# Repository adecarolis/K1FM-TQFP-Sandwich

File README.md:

# TQFP Sandwich

## A fully open sourced drop-in replacement for the [DL2MAN Sandwich](https://dl2man.de/)

This sligthly modified version of [Manuel DL2MAN](https://dl2man.de/)'s exceptional project was originally motivated by the need of a proper power connector and a TCXO. Subsequently an SWR meter and a 1.3" oled display were added.

### Boards

#### Main

- ATM328P on TQFP-32 footprint + all SMD components + single side, 2 layers design ($2 per 5 bare PCBs at JLCPCB)
- Available CPL and BOM files for rapid prototyping orders (~$39 for 5 fully assembled PCBs at JLCPCB ***)
- Round barrel jack connector compatible with the FT-817 (1.70mm ID - 4.00mm OD)
- Temperature Controlled Oscillator (TCXO) for absolute frequency precision (alignment no longer necessary)
- Extra 0 ohm resistors / contact pads for easier experimenting and troubleshooting

#### UI

- Accepts both 0.96" and 1.3" OLED displays
- Anti-bounce capacitors allowing for low-cost encoders being used
- Optional GPS receiver + antenna (not yet tested)
- Optional LM386 audio amplifier (not yet tested)

#### RF

- Compatible with DL2MAN REV3 standard RF boards
- Onboard SWR/Wattmeter
- High bands design: 10m, 15m, 20m, 30m, 40m
- SMD design allows for using either a single IRLML2060 or three MMBF170's (caps and toroids need to be matched accordingly)
- SMD Relays (Omron G6KU-2G-Y)

*** Parts not available (or currently not in stock) at LCSC that need to be sourced and installed separately: PJ-18H, Si5351, LM4562MAX, ASTX-H11-27.000MHZ-T, FST3253MTCX

### Testing

 This project is to be considered as experimental. If you are looking for stability and reliabiality, I'd recommend sticking to the original. 

| Board | Number built | Remarks                                                      | Issues                                                       |
| :---: | :----------: | ------------------------------------------------------------ | ------------------------------------------------------------ |
| Main  |      4       | - No performance differences from the original found yet.<br />- Only tested with OLED displays. |                                                              |
|  UI   |      5       | - Most 1.3" displays work normally but some require [a software patch](https://groups.io/g/ucx/message/5147?p=,,,20,0,0,0::Created,,reverted,20,2,0,79343439) (this would be the case for all UI boards, not just this particular one). | GPS and audio amplifier (both optional) not yet tested.      |
|  RF   |      1       | - Uses the REV3 IO Extender configuration with 3x SOT23 mosfets therefore passive components can be dimensioned after BS170/MMBF170's or IRLML2060's.<br />- [The SWR meter software](https://github.com/adecarolis/QCX-SSB/tree/swr-meter) modification currently only works for CW when using the straight key. | So far only tested on 20 meters and 40 meters using 3x BS170 mosfets: good performance on 20 meters, not good on 40. |

### License

Creative Commons 3.0

https://creativecommons.org/licenses/by-sa/3.0/

### Disclaimer

COVERED SOFTWARE IS PROVIDED UNDER THIS LICENSE ON AN "AS IS" BASIS, WITHOUT WARRANTY OF ANY KIND, EITHER EXPRESSED OR IMPLIED, INCLUDING, WITHOUT LIMITATION, WARRANTIES THAT THE COVERED SOFTWARE IS FREE OF DEFECTS, MERCHANTABLE, FIT FOR A PARTICULAR PURPOSE OR NON-INFRINGING. THE ENTIRE RISK AS TO THE QUALITY AND PERFORMANCE OF THE COVERED SOFTWARE IS WITH YOU. SHOULD ANY COVERED SOFTWARE PROVE DEFECTIVE IN ANY RESPECT, YOU (NOT THE INITIAL DEVELOPER OR ANY OTHER CONTRIBUTOR) ASSUME THE COST OF ANY NECESSARY SERVICING, REPAIR OR CORRECTION. THIS DISCLAIMER OF WARRANTY CONSTITUTES AN ESSENTIAL PART OF THIS LICENSE. NO USE OF ANY COVERED SOFTWARE IS AUTHORIZED HEREUNDER EXCEPT UNDER THIS DISCLAIMER.

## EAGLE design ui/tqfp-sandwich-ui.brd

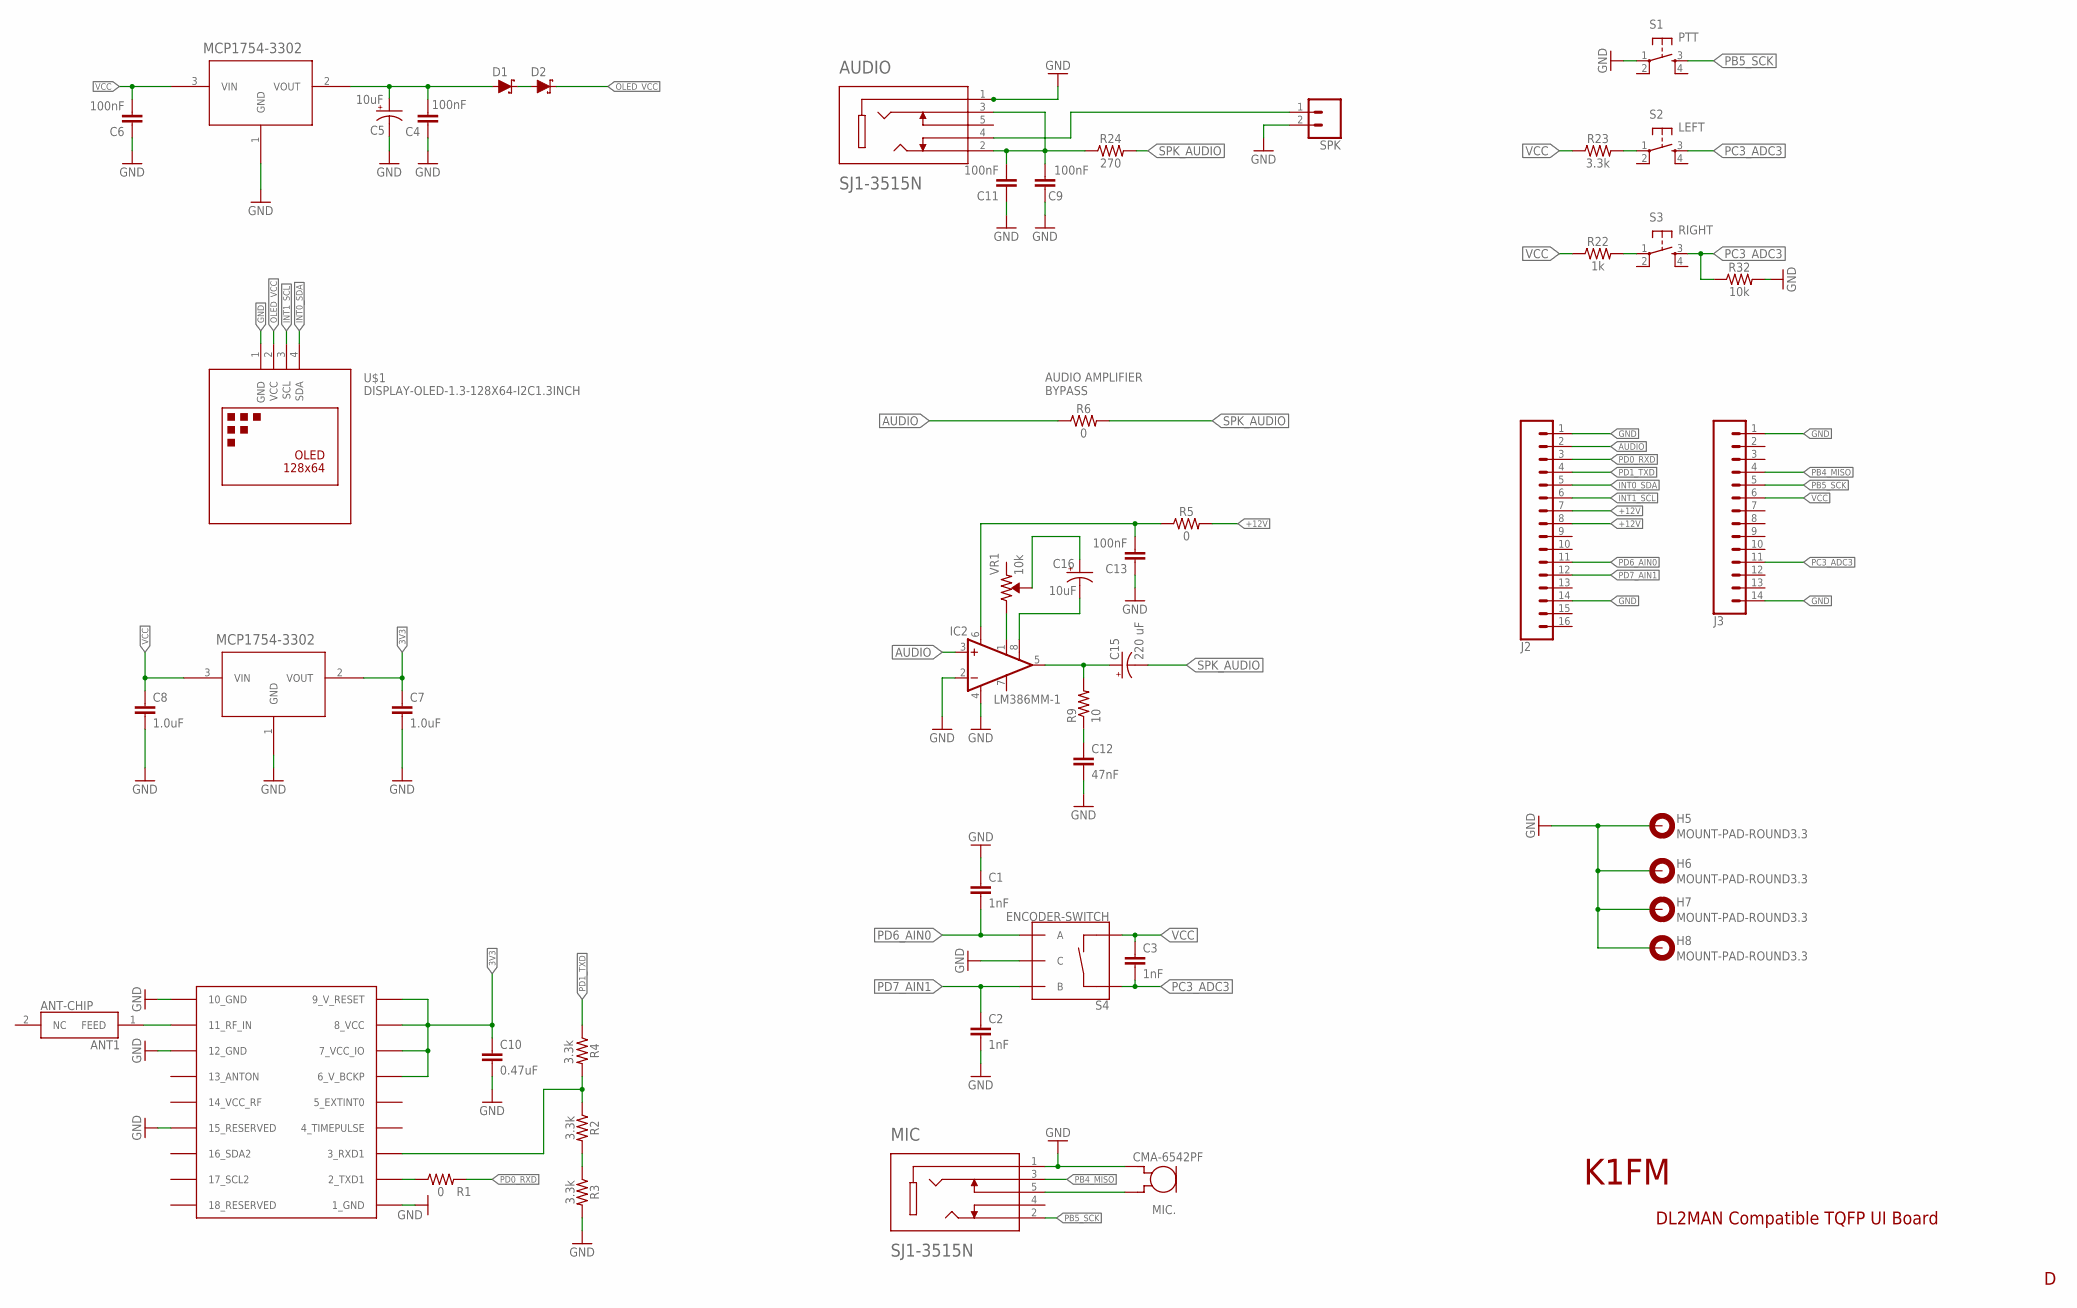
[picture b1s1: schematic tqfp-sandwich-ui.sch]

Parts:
ANT-CHIP: ANT1; 1575AT43A0040E
AUDIO: SJ1-3515N; CUI_SJ1-3515N
C1, C2, C3: 1nF; 0603
C4, C6, C9, C11, C13: 100nF; 0603
C5, C16: 10uF; EIA3216
C7, C8: 1.0uF; 0603
C10: 0.47uF; 0603
C12: 47nF; 0603
C15: 220 uF; PANASONIC_C
D1, D2: 1A/23V/620mV; SOD-323
GPS1: UBLOX_MAX
H5, H6, H7, H8: MOUNT-PAD-ROUND3.3; 3,3-PAD
IC2: LM386MM-1; MMSOP08
J2: CONN_16; 1X16
J3: CONN_14; 1X14
MIC: SJ1-3515N; CUI_SJ1-3515N
MIC.: CMA-6542PF; CUI_CMA-6542PF
R1, R5, R6: 0; 0603
R2, R3, R4, R23: 3.3k; 0603
R9: 10; 0603
R22: 1k; 0603
R24: 270; 0603
R32: 10k; 0603
S1: PTT; DTSM-6
S2: LEFT; DTSM-6
S3: RIGHT; DTSM-6
S4: ENCODER-SWITCH; ROTARY_ENC_PLAIN
SPK: CONN_02; 1X02
U1, U3: MCP1754X-XXXXX/C; SOT-23A_MC
U$1: DISPLAY-OLED-1.3-128X64-I2C1.3INCH; DISPLAY-OLED-1.3-128X64-I2C
VR1: 10k; TRIMPOT-SMD-TC33X

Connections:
3V3: C7.1, C10.1, GPS1.6_V_BCKP, GPS1.7_VCC_IO, GPS1.8_VCC, GPS1.9_V_RESET, U3.2 (VOUT)
+12V: J2.7, J2.8, R5.2
AUDIO: IC2.3 (+IN), J2.2, R6.1
GND: AUDIO.1, C1.1, C2.2, C4.1, C5.-, C6.1, C7.2, C8.2, C9.1, C10.2, C11.1, C12.2, C13.1, GPS1.1_GND, GPS1.10_GND, GPS1.12_GND, GPS1.15_RESERVED, H5.B3,3, H6.B3,3, H7.B3,3, H8.B3,3, IC2.2 (-IN), IC2.4 (GND), J2.1, J2.14, J3.1, J3.14, MIC.1, MIC..GND, R3.2, R32.2, S1.1, S4.C, SPK.2, U1.1 (GND), U3.1 (GND), U$1.1 (GND)
INT0_SDA: J2.5, U$1.4 (SDA)
INT1_SCL: J2.6, U$1.3 (SCL)
unnamed: GPS1.2_TXD1, R1.1
unnamed: MIC.5, MIC..OUT
unnamed: GPS1.3_RXD1, R2.1, R4.2
unnamed: R23.2, S2.1
unnamed: R2.2, R3.1
unnamed: ANT-CHIP.1 (FEED), GPS1.11_RF_IN
unnamed: D1.C, D2.A
unnamed: C4.2, C5.+, D1.A, U1.2 (VOUT)
unnamed: C12.1, R9.1
unnamed: AUDIO.4, SPK.1
unnamed: C15.+, IC2.5 (OUT), R9.2
unnamed: IC2.1 (GAIN), VR1.1 (CW)
unnamed: C16.+, VR1.2 (WIPER)
unnamed: C16.-, IC2.8 (GAIN)
unnamed: C13.2, IC2.6 (VS), R5.1
unnamed: R22.2, S3.1
unnamed: AUDIO.2, AUDIO.3, C9.2, C11.2, R24.1
OLED_VCC: D2.C, U$1.2 (VCC)
PB4_MISO: J3.4, MIC.3
PB5_SCK: J3.5, MIC.2, S1.3
PC3_ADC3: C3.2, J3.11, R32.1, S2.3, S3.3, S4.SW+
PD0_RXD: J2.3, R1.2
PD1_TXD: J2.4, R4.1
PD6_AIN0: C1.2, J2.11, S4.A
PD7_AIN1: C2.1, J2.12, S4.B
SPK_AUDIO: C15.-, R6.2, R24.2
VCC: C3.1, C6.2, C8.1, J3.6, R22.1, R23.1, S4.SW-, U1.3 (VIN), U3.3 (VIN)

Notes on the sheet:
DL2MAN Compatible TQFP UI Board
K1FM
AUDIO AMPLIFIER BYPASS

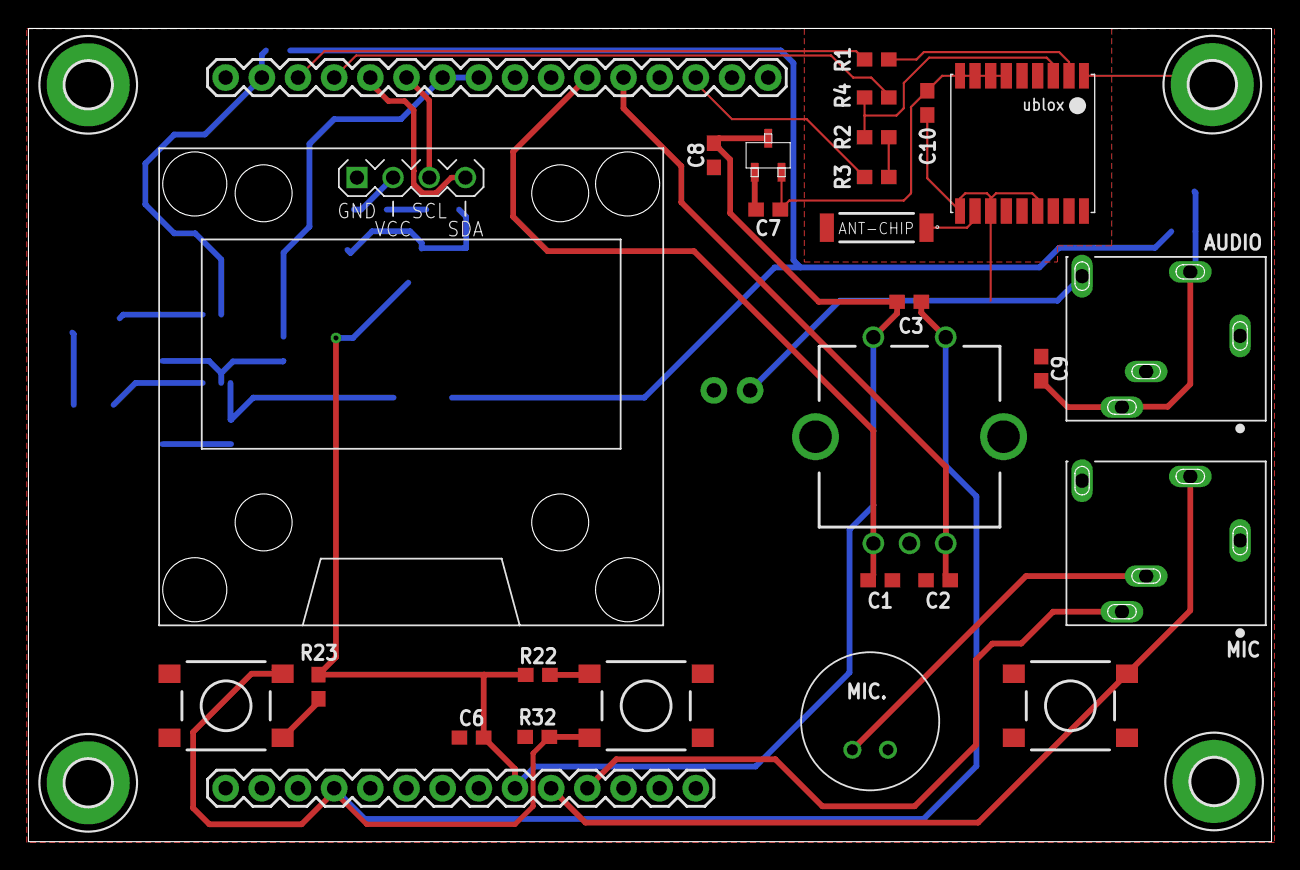
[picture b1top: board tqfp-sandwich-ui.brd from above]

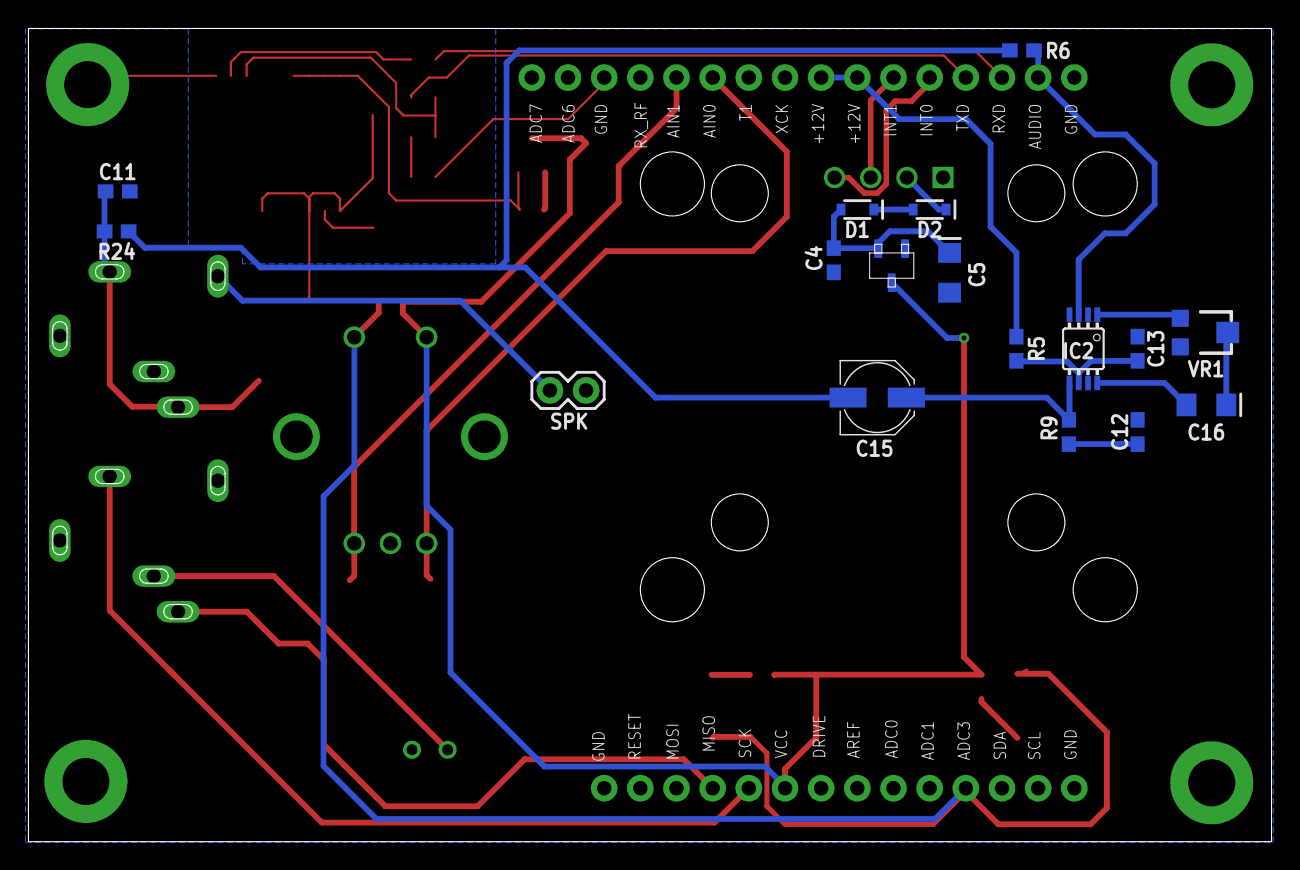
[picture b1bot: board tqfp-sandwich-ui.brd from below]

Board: 2 copper layers, 87.3 x 57.1 mm, 49 parts (17 on the bottom side), 33 nets.

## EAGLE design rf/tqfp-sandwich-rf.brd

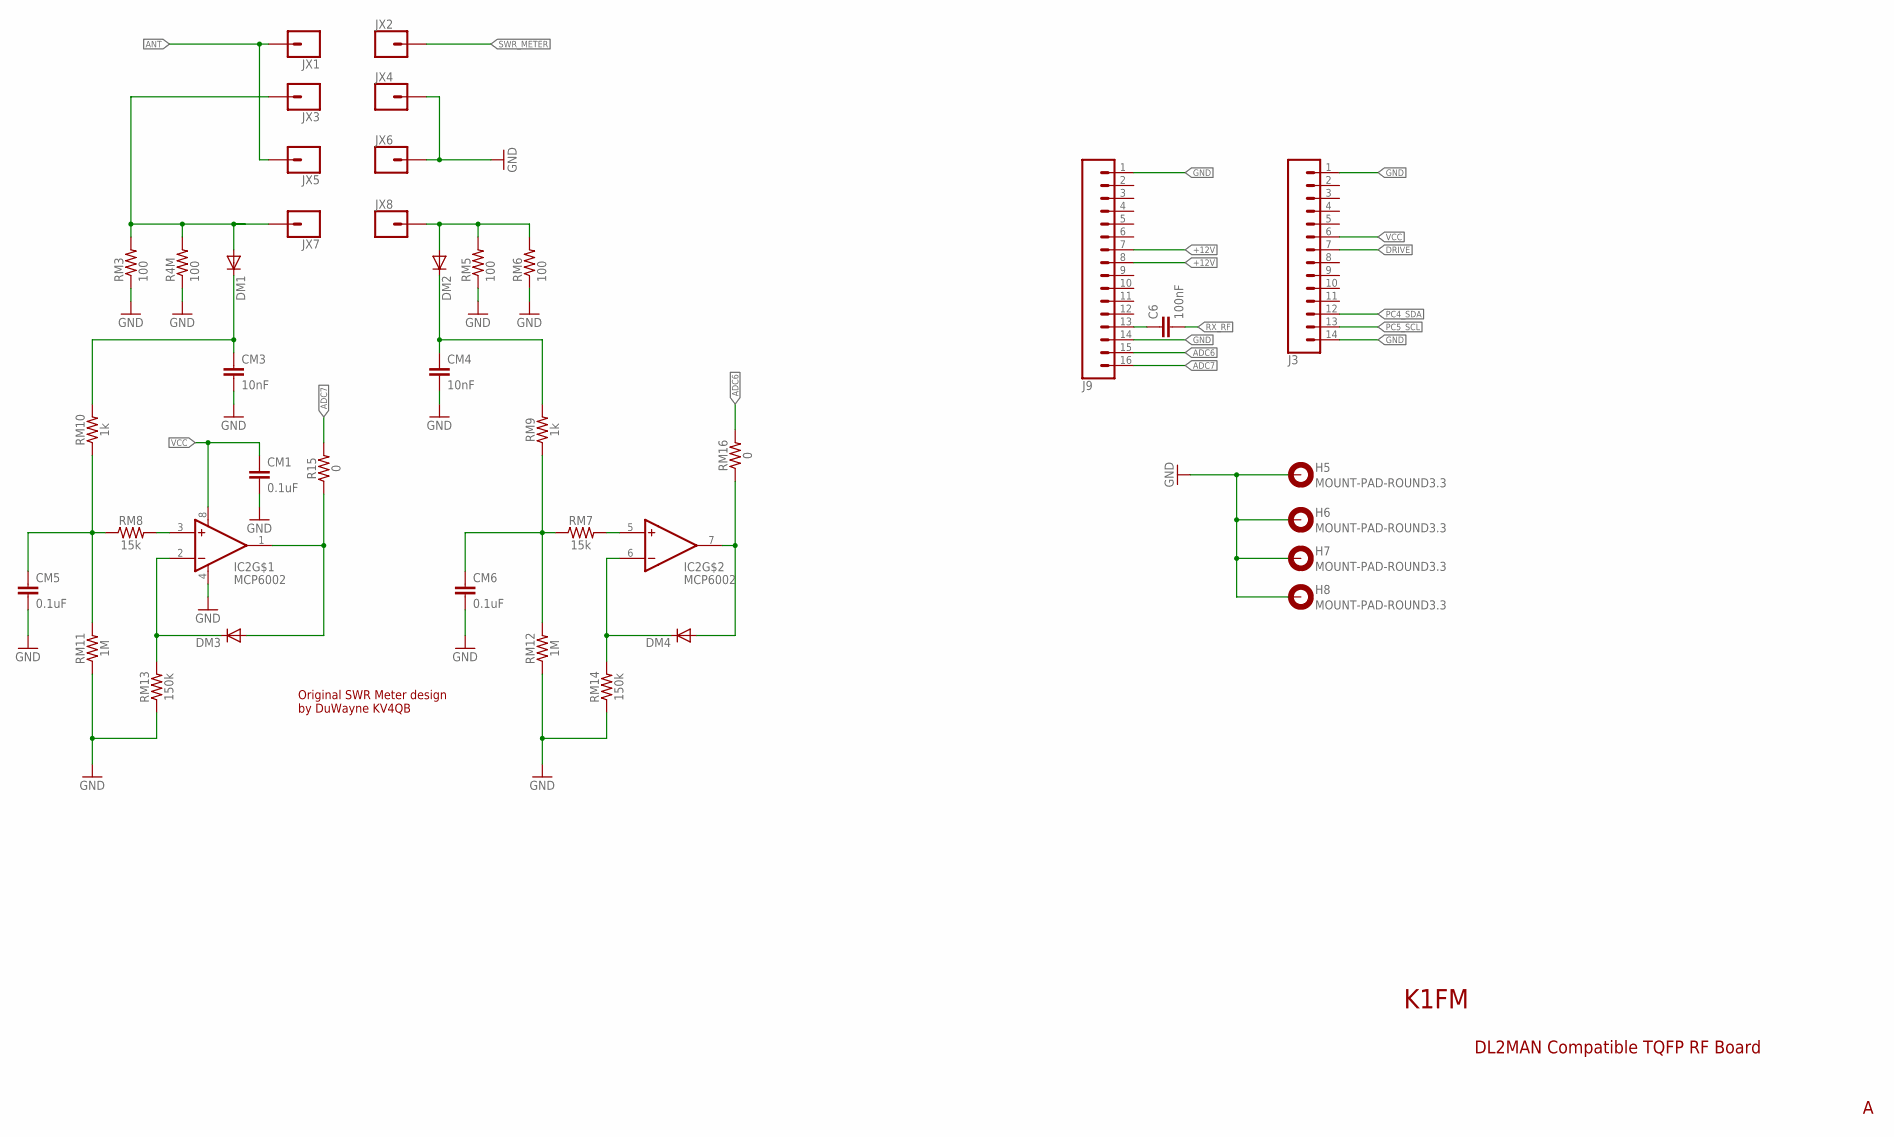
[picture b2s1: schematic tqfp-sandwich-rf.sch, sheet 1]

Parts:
C6: 100nF; RESC0805_L
CM1, CM5, CM6: 0.1uF; 0603
CM3, CM4: 10nF; 0603
DM1, DM2, DM3, DM4: 1N60P; DO35-10
H5, H6, H7, H8: MOUNT-PAD-ROUND3.3; 3,3-PAD
IC2: MCP6002; SOIC8
J3: CONN_14; 1X14
J9: CONN_16; 1X16
JX1, JX2, JX3, JX4, JX5, JX6, JX7, JX8: CONN_01; 1X01
R4M: 100; M1206
R15: 0; 0603
RM3, RM5, RM6: 100; M1206
RM7, RM8: 15k; 0603
RM9, RM10: 1k; 0603
RM11, RM12: 1M; 0603
RM13, RM14: 150k; 0603
RM16: 0; 0603

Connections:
+12V: J9.7, J9.8; also elsewhere on the board
ADC6: J9.15, RM16.2
ADC7: J9.16, R15.2
ANT: JX1.1, JX5.1; also elsewhere on the board
DRIVE: J3.7; also elsewhere on the board
GND: CM1.2, CM3.2, CM4.2, CM5.2, CM6.2, H5.B3,3, H6.B3,3, H7.B3,3, H8.B3,3, IC2.4 (V-), J3.1, J3.14, J9.1, J9.14, JX4.1, JX6.1, R4M.1, RM3.1, RM5.1, RM6.1, RM11.1, RM12.1, RM13.1, RM14.1; also elsewhere on the board
unnamed: DM3.A, IC2.1 (OUT), R15.1
unnamed: DM4.A, IC2.7 (OUT), RM16.1
unnamed: C6.1, J9.13
unnamed: DM1.A, JX3.1, JX7.1, R4M.2, RM3.2
unnamed: DM2.A, JX8.1, RM5.2, RM6.2
unnamed: CM3.1, DM1.C, RM10.2
unnamed: CM4.1, DM2.C, RM9.2
unnamed: DM3.C, IC2.2 (-IN), RM13.2
unnamed: DM4.C, IC2.6 (-IN), RM14.2
unnamed: IC2.3 (+IN), RM8.2
unnamed: IC2.5 (+IN), RM7.2
unnamed: CM6.1, RM7.1, RM9.1, RM12.2
unnamed: CM5.1, RM8.1, RM10.1, RM11.2
PC4_SDA: J3.12; also elsewhere on the board
PC5_SCL: J3.13; also elsewhere on the board
RX_RF: C6.2; also elsewhere on the board
SWR_METER: JX2.1; also elsewhere on the board
VCC: CM1.1, IC2.8 (V+), J3.6; also elsewhere on the board

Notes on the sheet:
DL2MAN Compatible TQFP RF Board
K1FM
Original SWR Meter design by DuWayne KV4QB

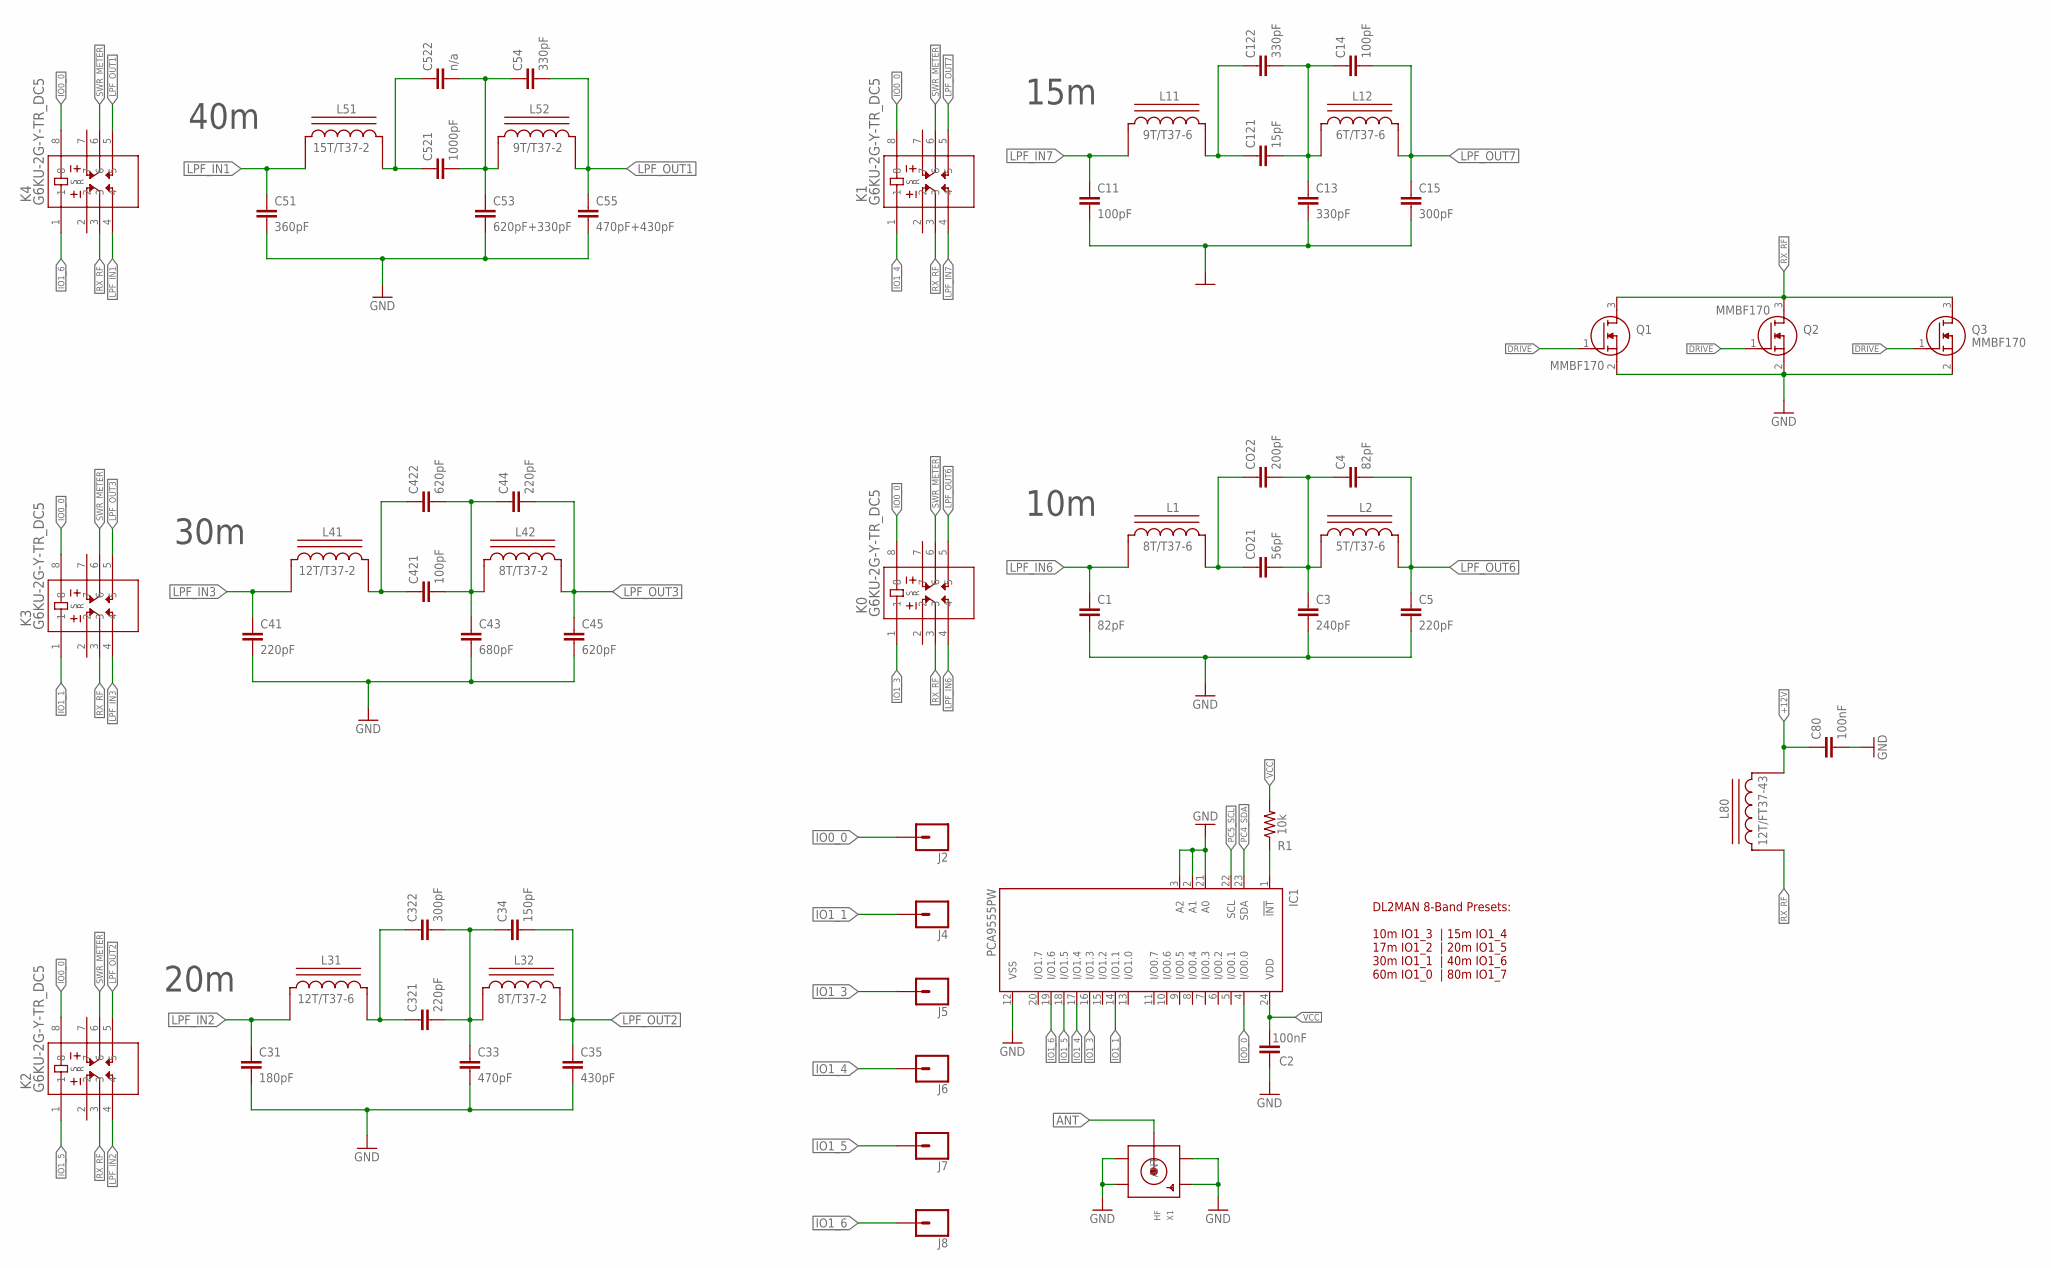
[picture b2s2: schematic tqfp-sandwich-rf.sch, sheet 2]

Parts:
C1, C4: 82pF; RESC0805_L
C2, C80: 100nF; RESC0805_L
C3: 240pF; RESC0805_L
C5, C41, C44, C321: 220pF; RESC0805_L
C11, C14, C421: 100pF; RESC0805_L
C13, C54, C122: 330pF; RESC0805_L
C15, C322: 300pF; RESC0805_L
C31: 180pF; RESC0805_L
C33: 470pF; RESC0805_L
C34: 150pF; RESC0805_L
C35: 430pF; RESC0805_L
C43: 680pF; RESC0805_L
C45, C422: 620pF; RESC0805_L
C51: 360pF; RESC0805_L
C53: 620pF+330pF; RESC0805_L
C55: 470pF+430pF; RESC0805_L
C121: 15pF; RESC0805_L
C521: 1000pF; RESC0805_L
C522: n/a; RESC0805_L
CO21: 56pF; RESC0805_L
CO22: 200pF; RESC0805_L
IC1: PCA9555PW; TSSOP24
J2, J4, J5, J6, J7, J8: CONN_01OFFSET; 1X01_OFFSET
K0, K1, K2, K3, K4: G6KU-2G-Y-TR_DC5; G6KU-2G-Y_DC3_OMR
L1: 8T/T37-6; T37_INDUCTOR
L2: 5T/T37-6; T37_INDUCTOR
L11: 9T/T37-6; T37_INDUCTOR
L12: 6T/T37-6; T37_INDUCTOR
L31: 12T/T37-6; T37_INDUCTOR
L32, L42: 8T/T37-2; T37_INDUCTOR
L41: 12T/T37-2; T37_INDUCTOR
L51: 15T/T37-2; T37_INDUCTOR
L52: 9T/T37-2; T37_INDUCTOR
L80: 12T/FT37-43; T37_INDUCTOR
Q1, Q2, Q3: MMBF170; SOT96P237X111-3N
R1: 10k; 0603
X1: HF; SMA_EDGELAUNCH

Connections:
+12V: C80.1, L80.CA; also elsewhere on the board
ANT: X1.P (ANT); also elsewhere on the board
DRIVE: Q1.1 (G), Q2.1 (G), Q3.1 (G); also elsewhere on the board
GND: C1.2, C2.1, C3.2, C5.2, C11.2, C13.2, C15.2, C31.2, C33.2, C35.2, C41.2, C43.2, C45.2, C51.2, C53.2, C55.2, C80.2, IC1.2 (A1), IC1.3 (A2), IC1.12 (VSS), IC1.21 (A0), Q1.2 (S), Q2.2 (S), Q3.2 (S), X1.GND@1 (GND4), X1.GND@2 (GND3), X1.GND@3 (GND2), X1.GND@4 (GND1); also elsewhere on the board
IO0_0: IC1.4 (I/O0.0), J2.1, K0.8, K1.8, K2.8, K3.8, K4.8
IO1_1: IC1.14 (I/O1.1), J4.1, K3.1
IO1_3: IC1.16 (I/O1.3), J5.1, K0.1
IO1_4: IC1.17 (I/O1.4), J6.1, K1.1
IO1_5: IC1.18 (I/O1.5), J7.1, K2.1
IO1_6: IC1.19 (I/O1.6), J8.1, K4.1
LPF_IN1: C51.1, K4.4, L51.CB
LPF_IN2: C31.1, K2.4, L31.CB
LPF_IN3: C41.1, K3.4, L41.CB
LPF_IN6: C1.1, K0.4, L1.CB
LPF_IN7: C11.1, K1.4, L11.CB
LPF_OUT1: C54.2, C55.1, K4.5, L52.CA
LPF_OUT2: C34.2, C35.1, K2.5, L32.CA
LPF_OUT3: C44.2, C45.1, K3.5, L42.CA
LPF_OUT6: C4.2, C5.1, K0.5, L2.CA
LPF_OUT7: C14.2, C15.1, K1.5, L12.CA
unnamed: CO21.1, CO22.1, L1.CA
unnamed: C3.1, C4.1, CO21.2, CO22.2, L2.CB
unnamed: C121.1, C122.1, L11.CA
unnamed: C13.1, C14.1, C121.2, C122.2, L12.CB
unnamed: IC1.1 (!INT), R1.1
unnamed: C421.1, C422.1, L41.CA
unnamed: C43.1, C44.1, C421.2, C422.2, L42.CB
unnamed: C321.1, C322.1, L31.CA
unnamed: C33.1, C34.1, C321.2, C322.2, L32.CB
unnamed: C521.1, C522.1, L51.CA
unnamed: C53.1, C54.1, C521.2, C522.2, L52.CB
PC4_SDA: IC1.23 (SDA); also elsewhere on the board
PC5_SCL: IC1.22 (SCL); also elsewhere on the board
RX_RF: K0.3, K1.3, K2.3, K3.3, K4.3, L80.CB, Q1.3 (D), Q2.3 (D), Q3.3 (D); also elsewhere on the board
SWR_METER: K0.6, K1.6, K2.6, K3.6, K4.6; also elsewhere on the board
VCC: C2.2, IC1.24 (VDD), R1.2; also elsewhere on the board

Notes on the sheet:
20m
40m
30m
10m
15m
DL2MAN 8-Band Presets: 10m IO1_3 | 15m IO1_4 17m IO1_2 | 20m IO1_5 30m IO1_1 | 40m IO1_6 60m IO1_0 | 80m IO1_7

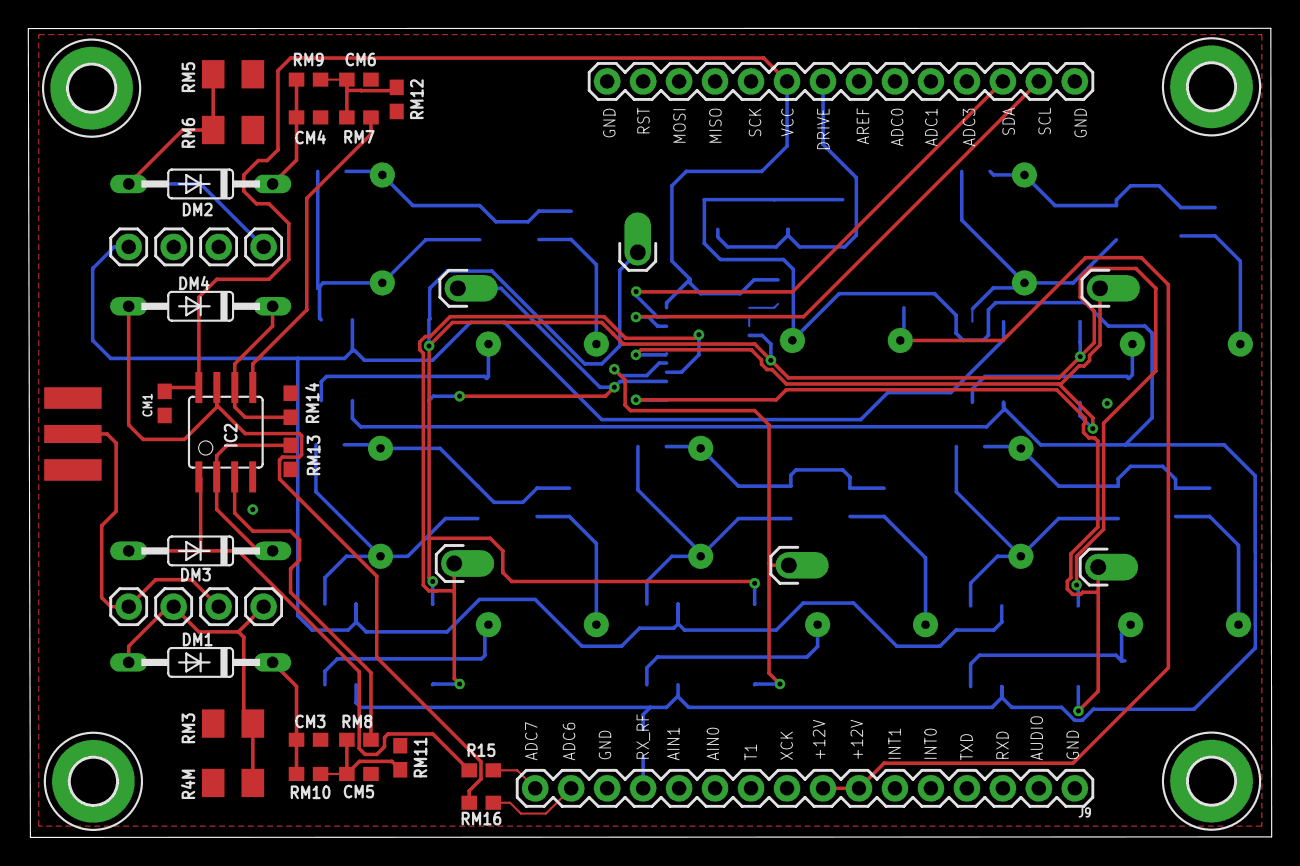
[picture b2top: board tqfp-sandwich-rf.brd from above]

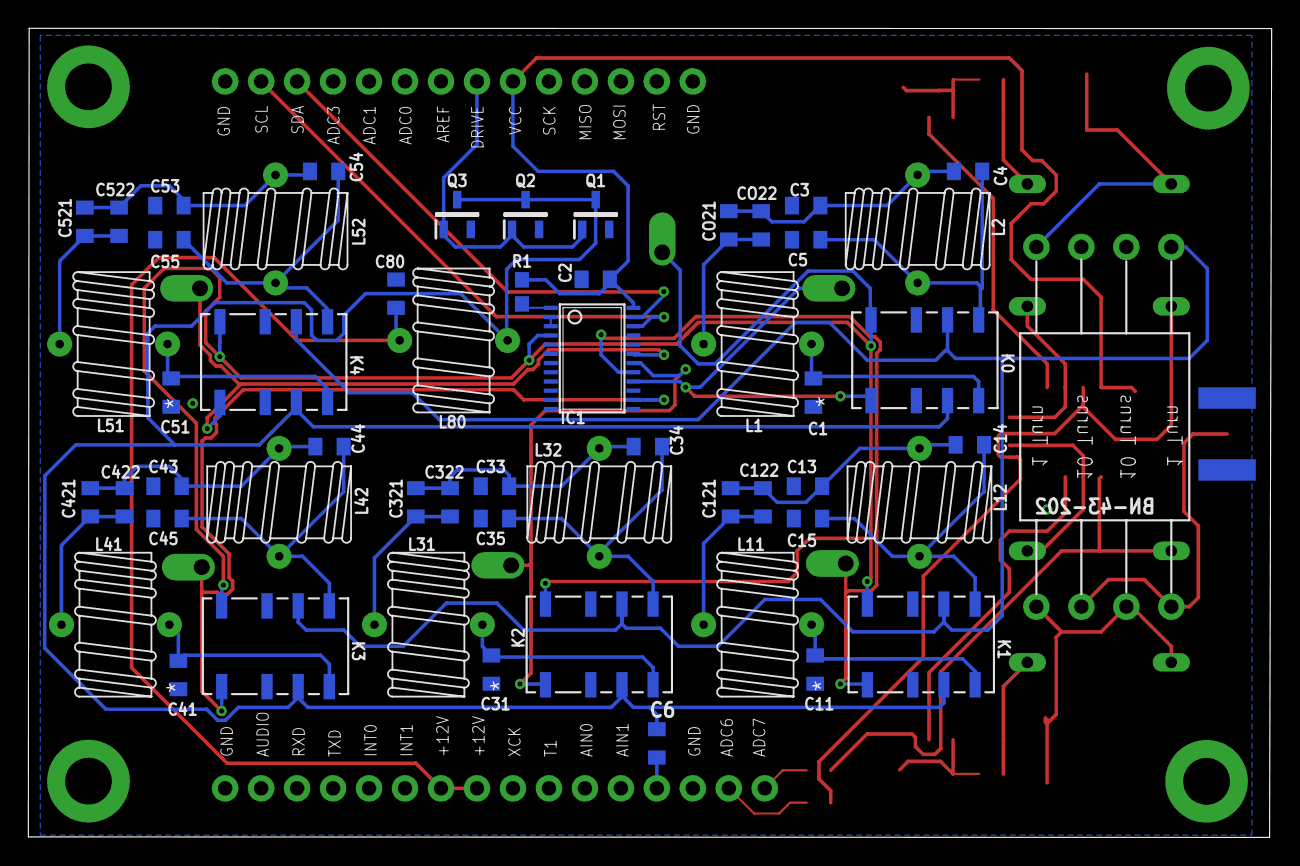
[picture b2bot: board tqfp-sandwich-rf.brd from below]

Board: 2 copper layers, 87.8 x 57.1 mm, 99 parts (54 on the bottom side), 51 nets.

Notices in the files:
parts and their libraries:
SparkFun-Connectors: Licensing: Creative Commons ShareAlike 4.0 International - https://creativecommons.org/licenses/by-sa/4.0
microbuilder: This work is placed in the public domain, and may be freely used for commercial and non-commercial work with the following conditions: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
